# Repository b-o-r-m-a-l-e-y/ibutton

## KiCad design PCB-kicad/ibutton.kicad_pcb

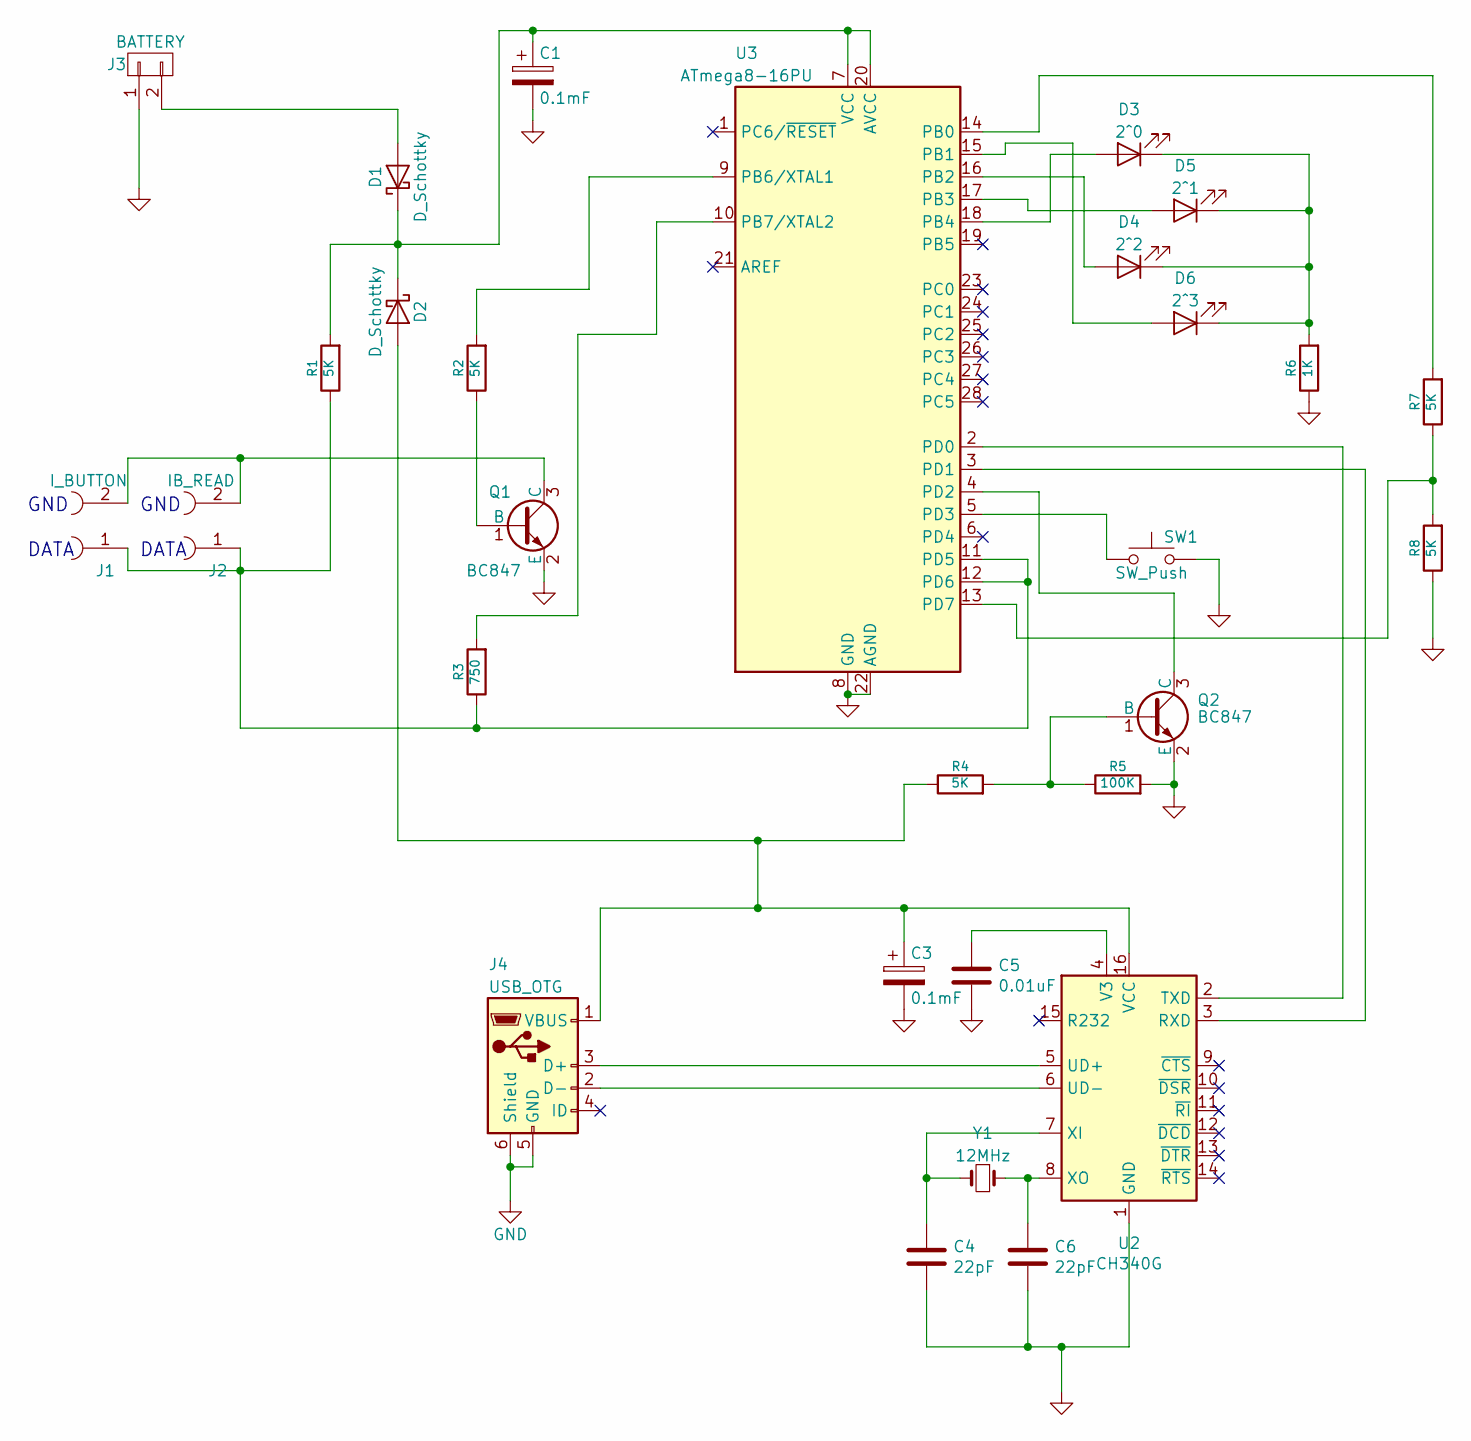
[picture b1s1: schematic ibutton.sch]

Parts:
C1, C3: 0.1mF; C_0805_2012Metric_Pad1.15x1.40mm_HandSolder
C4, C6: 22pF; C_0805_2012Metric_Pad1.15x1.40mm_HandSolder
C5: 0.01uF; C_0805_2012Metric_Pad1.15x1.40mm_HandSolder
D1, D2: D_Schottky; D_SOT-23_NKA
D3: 2^0; LED_D5.0mm
D4: 2^2; LED_D5.0mm
D5: 2^1; LED_D5.0mm
D6: 2^3; LED_D5.0mm
J1: I_BUTTON; PinHeader_1x02_P2.54mm_Vertical
J2: IB_READ; PinHeader_1x02_P2.54mm_Vertical
J3: BATTERY; PinHeader_1x02_P2.54mm_Vertical
J4: USB_OTG; USB_Micro-B_Wuerth_629105150521
Q1, Q2: BC847; SOT-23_Handsoldering
R1, R2, R4, R7, R8: 5K; R_0805_2012Metric_Pad1.15x1.40mm_HandSolder
R3: 750; R_0805_2012Metric_Pad1.15x1.40mm_HandSolder
R5: 100K; R_0805_2012Metric_Pad1.15x1.40mm_HandSolder
R6: 1K; R_0805_2012Metric_Pad1.15x1.40mm_HandSolder
SW1: SW_Push; SW_SPST_PTS645
U2: CH340G; SOIC-16_3.9x9.9mm_P1.27mm
U3: ATmega8-16PU; DIP-28_W7.62mm
Y1: 12MHz; Crystal_SMD_HC49-SD

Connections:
GND: C1.2, C3.2, C4.2, C5.2, C6.2, J3.1, J4.5 (GND), J4.6 (Shield), Q1.2 (E), Q2.2 (E), R5.2, R6.1, R8.1, SW1.2, U2.1 (GND), U3.8 (GND), U3.22 (AGND)
unnamed: C1.1, D1.1 (K), D2.1 (K), R1.2, U3.7 (VCC), U3.20 (AVCC)
unnamed: C3.1, D2.2 (A), J4.1 (VBUS), R4.1, U2.16 (VCC)
unnamed: C4.1, U2.7 (XI), Y1.2
unnamed: C5.1, U2.4 (V3)
unnamed: C6.1, U2.8 (XO), Y1.1
unnamed: D1.2 (A), J3.2
unnamed: D3.1 (K), D4.1 (K), D5.1 (K), D6.1 (K), R6.2
unnamed: D3.2 (A), U3.18 (PB4)
unnamed: D4.2 (A), U3.16 (PB2)
unnamed: D5.2 (A), U3.17 (PB3)
unnamed: D6.2 (A), U3.15 (PB1)
unnamed: J1.1, J2.1, R1.1, R3.1, U3.11 (PD5), U3.12 (PD6)
unnamed: J1.2, J2.2, Q1.3 (C)
unnamed: J4.2 (D-), U2.6 (UD-)
unnamed: J4.3 (D+), U2.5 (UD+)
unnamed: Q1.1 (B), R2.1
unnamed: Q2.1 (B), R4.2, R5.1
unnamed: Q2.3 (C), U3.4 (PD2)
unnamed: R2.2, U3.9 (PB6/XTAL1)
unnamed: R3.2, U3.10 (PB7/XTAL2)
unnamed: R7.1, R8.2, U3.13 (PD7)
unnamed: R7.2, U3.14 (PB0)
unnamed: SW1.1, U3.5 (PD3)
unnamed: U2.2 (TXD), U3.2 (PD0)
unnamed: U2.3 (RXD), U3.3 (PD1)

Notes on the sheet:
GND
DATA

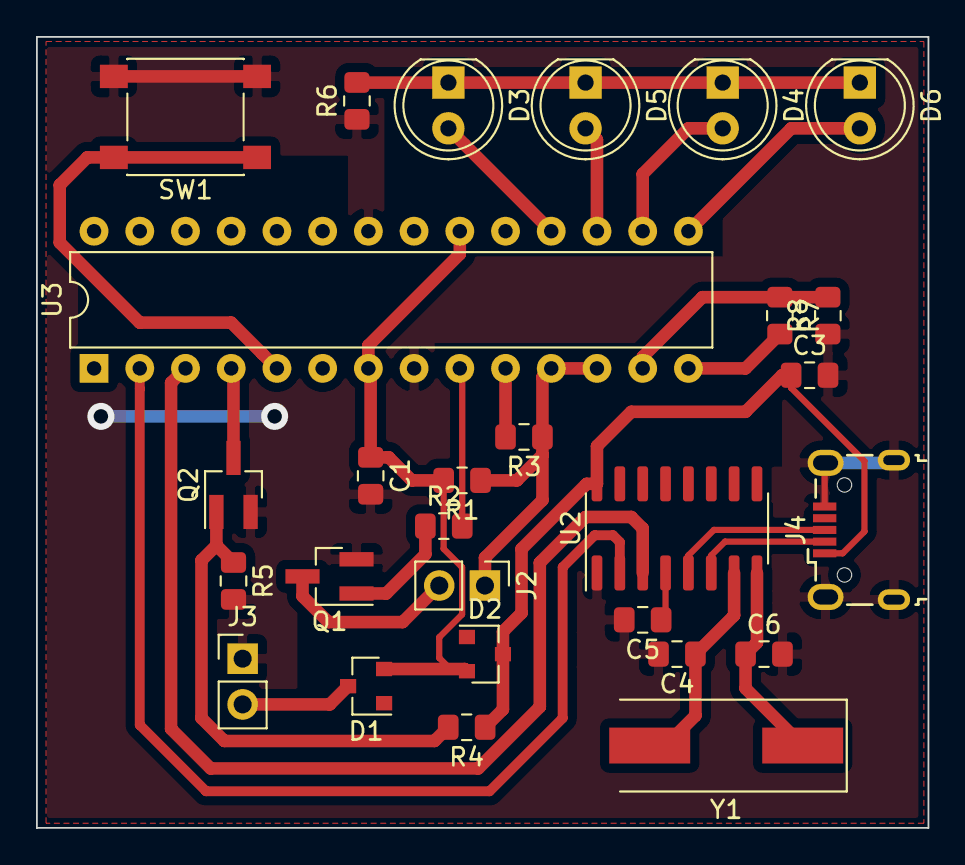
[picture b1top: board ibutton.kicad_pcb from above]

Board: 2 copper layers, 49.5 x 43.9 mm, 28 parts (0 on the bottom side), 26 nets.

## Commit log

2020-05-07 remake CH340
    started schematics
2020-05-07 разработка печатной платы
2020-05-07 готов прототип печатной платы
2020-05-07 версия печатной платы поменьше
2020-05-07 небольшой фикс
2020-05-09 invalid footprint
2020-05-10 нормальная печатная плата
2020-05-13 немножко пофиксил печатную плату
    и начерчен svg
2020-05-13 invalid footprint & code rework
2020-05-26 compiled
2020-05-27 not working yet
2020-06-02 заменил ключ в вездеходе
